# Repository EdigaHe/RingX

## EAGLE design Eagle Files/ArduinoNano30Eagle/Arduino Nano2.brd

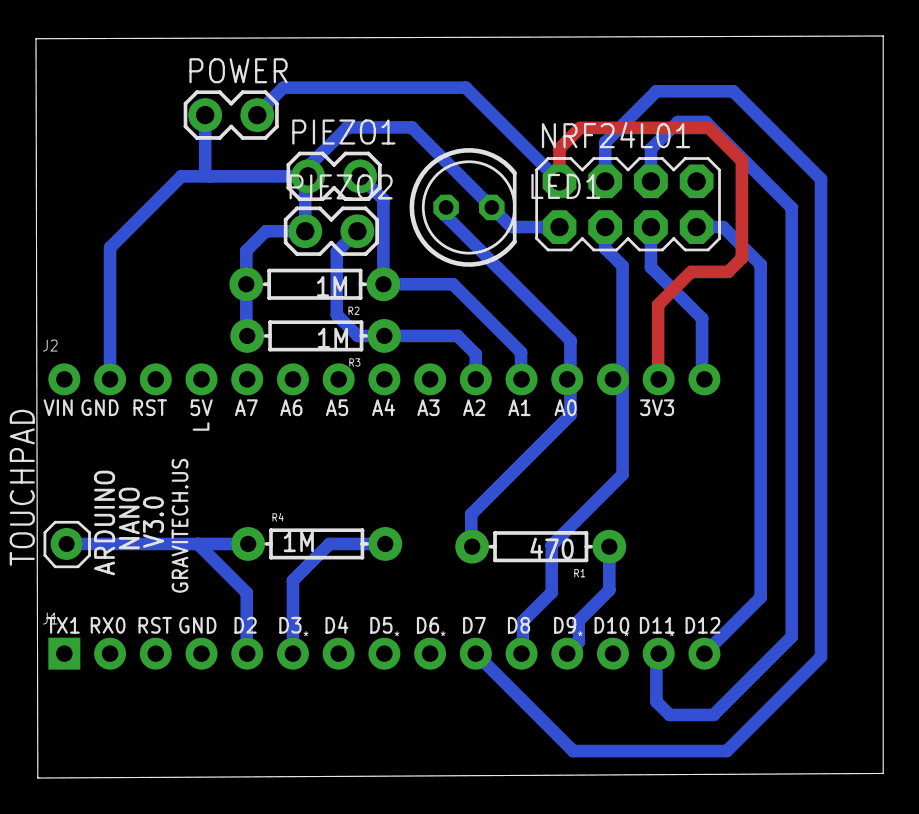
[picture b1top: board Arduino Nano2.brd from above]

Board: 2 copper layers, 47.1 x 41.2 mm, 12 parts (0 on the bottom side), 13 nets.

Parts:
J1: HEAD15-NOSS
J2: HEAD15-NOSS-1
LED1: LED_LED5MM
NRF24L01: M04X2; 2X4
PIEZO1, PIEZO2: 1X02_LOCK
POWER: 1X02_LOCK
R1: 470; AXIAL-0.3
R2, R3, R4: 1M; AXIAL-0.3
TOUCHPAD: M01PTH; 1X01

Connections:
A1: J2.11, PIEZO1.2, R2.P$1
A2: J2.10, PIEZO2.2, R3.P$1
CE: J1.11, NRF24L01.3
CSN: J1.10, NRF24L01.4
D2: J1.5, R4.P$1, TOUCHPAD.1
D3: J1.6, R4.P$2
GND: J2.2, LED1.K, NRF24L01.1, PIEZO1.1, PIEZO2.1, POWER.1, R2.P$2, R3.P$2
LED: J1.12, R1.P$1
MISO: J1.15, NRF24L01.7
MOSI: J1.14, NRF24L01.6
unnamed: LED1.A, R1.P$2
SCK: J2.15, NRF24L01.5
VCC: J2.14, NRF24L01.2, POWER.2

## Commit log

2014-11-06 code+supplementary files
    add source code, 3d model file, photos and instructions.

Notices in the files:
parts and their libraries:
SparkFun: Licensing: CC v3.0 Share-Alike You are welcome to use this library for commercial purposes.
